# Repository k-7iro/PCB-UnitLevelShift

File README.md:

# PCB-LogicShifterUnit
This logic level shifter has the same shape as the M5Stack Unit and can be used to connect the M5Stack Unit or M5Stack Controller (Core, Atom, etc) to an Arduino.

## Specification
The side marked "LV 3.3V" allows you to solder 2mm pitch 4-pin connectors. This includes Grove connectors and PH connectors. The signal voltage is 3.3V. Please note that the power supply voltage is 5V.

The side marked "HV 5V" allows you to solder 2.54mm pitch 4-pin connectors. This includes common pin headers and XH connectors. The signal voltage is 5V.

There is no specification for the direction of the power supply or signal. Signals are pulled up. Analog signals cannot be handled.

## Pinout Tips
| LV-Side Device | HV-Side A | HV-Side B |
| ---- | ---- | ---- |
| M5Stack Controller & Unit (I2C) | SDA | SCL |
| M5Stack Controller (UART) | LV:TxD HV:RxD *1 | LV:RxD HV:TxD *1 |
| M5Stack Unit (UART) | LV:RxD HV:TxD *1 | LV:TxD HV:RxD *1 |
| M5Stack Controller & Unit (GPIO) | *2 | *2 |

- *1: In the case of LV:TxD HV:RxD, connect the RxD pin of the Arduino or any microcontroller to HV-Side A, and vice versa.
- *2: For Controller, please check the your source code, and for Unit, please check the product page.

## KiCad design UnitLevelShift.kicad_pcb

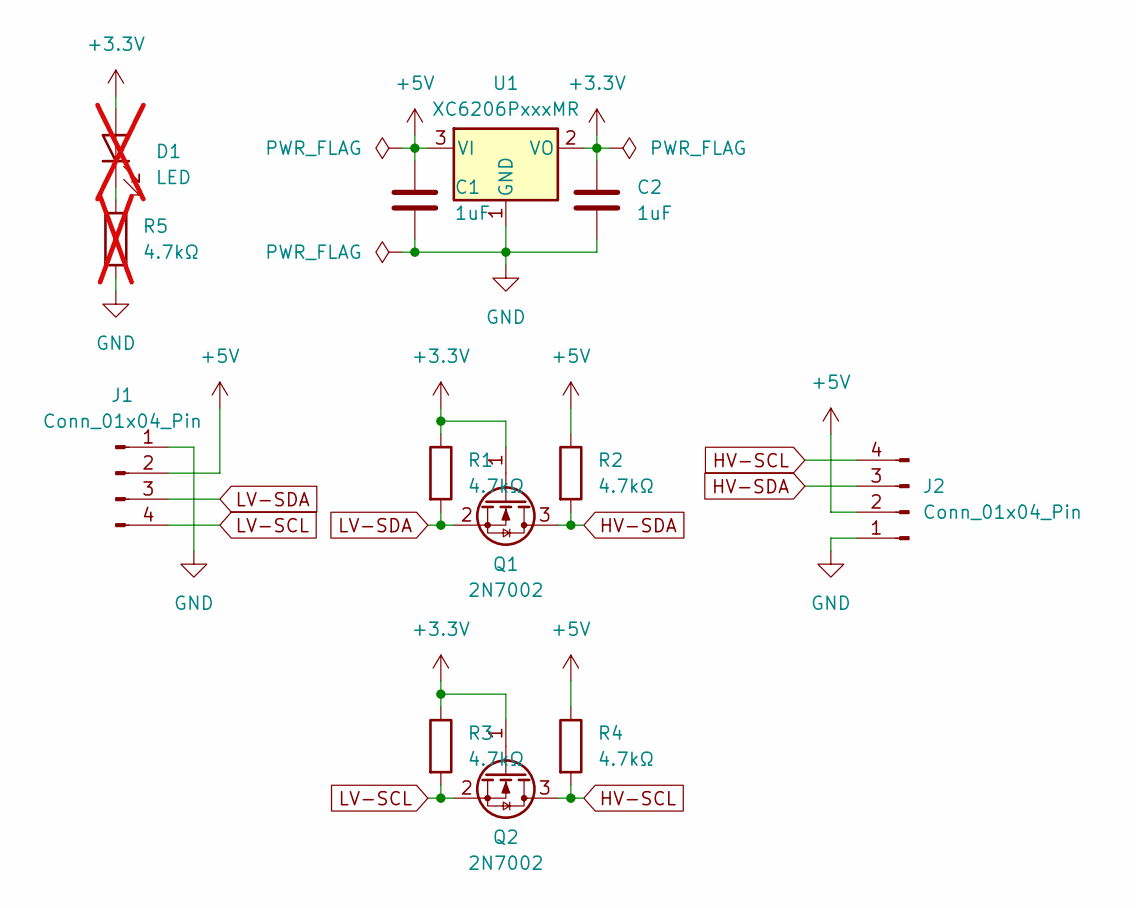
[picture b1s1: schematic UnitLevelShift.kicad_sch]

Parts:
C1, C2: 1uF; C_0402_1005Metric
D1: LED; LED_D3.0mm; not fitted
J1: Conn_01x04_Pin; JST_PH_S4B-PH-K_1x04_P2.00mm_Horizontal
J2: Conn_01x04_Pin; PinHeader_1x04_P2.54mm_Vertical
Q1, Q2: 2N7002; SOT-23
R1, R2, R3, R4: 4.7kΩ; R_0402_1005Metric
R5: 4.7kΩ; R_Axial_DIN0204_L3.6mm_D1.6mm_P2.54mm_Vertical; not fitted
U1: XC6206PxxxMR; SOT-23-3

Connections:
+3.3V: C2.1, D1.2 (A), Q1.1 (G), Q2.1 (G), R1.1, R3.1, U1.2 (VO)
+5V: C1.1, J1.2, J2.2, R2.1, R4.1, U1.3 (VI)
GND: C1.2, C2.2, J1.1, J2.1, R5.2, U1.1 (GND)
HV-SCL: J2.4, Q2.3 (D), R4.2
HV-SDA: J2.3, Q1.3 (D), R2.2
LV-SCL: J1.4, Q2.2 (S), R3.2
LV-SDA: J1.3, Q1.2 (S), R1.2
unnamed: D1.1 (K), R5.1

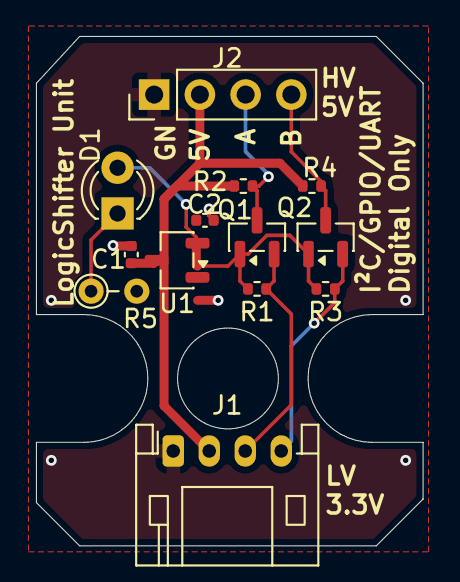
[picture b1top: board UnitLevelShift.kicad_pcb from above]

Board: 2 copper layers, 21.5 x 28.3 mm, 13 parts (0 on the bottom side), 8 nets.

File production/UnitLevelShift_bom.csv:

Designator,Footprint,Quantity,Value,LCSC Part #
"C1, C2",0402,2,1uF,
D1,LED_D3.0mm,1,LED,
J1,JST_PH_S4B-PH-K_1x04_P2.00mm_Horizontal,1,Conn_01x04_Pin,
J2,PinHeader_1x04_P2.54mm_Vertical,1,Conn_01x04_Pin,
"Q1, Q2",SOT-23,2,2N7002,
"R1, R2, R3, R4",0402,4,4.7kΩ,
R5,R_Axial_DIN0204_L3.6mm_D1.6mm_P2.54mm_Vertical,1,4.7kΩ,
U1,SOT-23-3,1,XC6206PxxxMR,

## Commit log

2026-01-05 Added V1 Schematics and PCB
2026-01-05 Revise README for PCB-LogicShifterUnit details
    Updated the README to reflect the correct product name and added specifications and pinout tips.
2026-04-09 Changed LED to optional mounting.
